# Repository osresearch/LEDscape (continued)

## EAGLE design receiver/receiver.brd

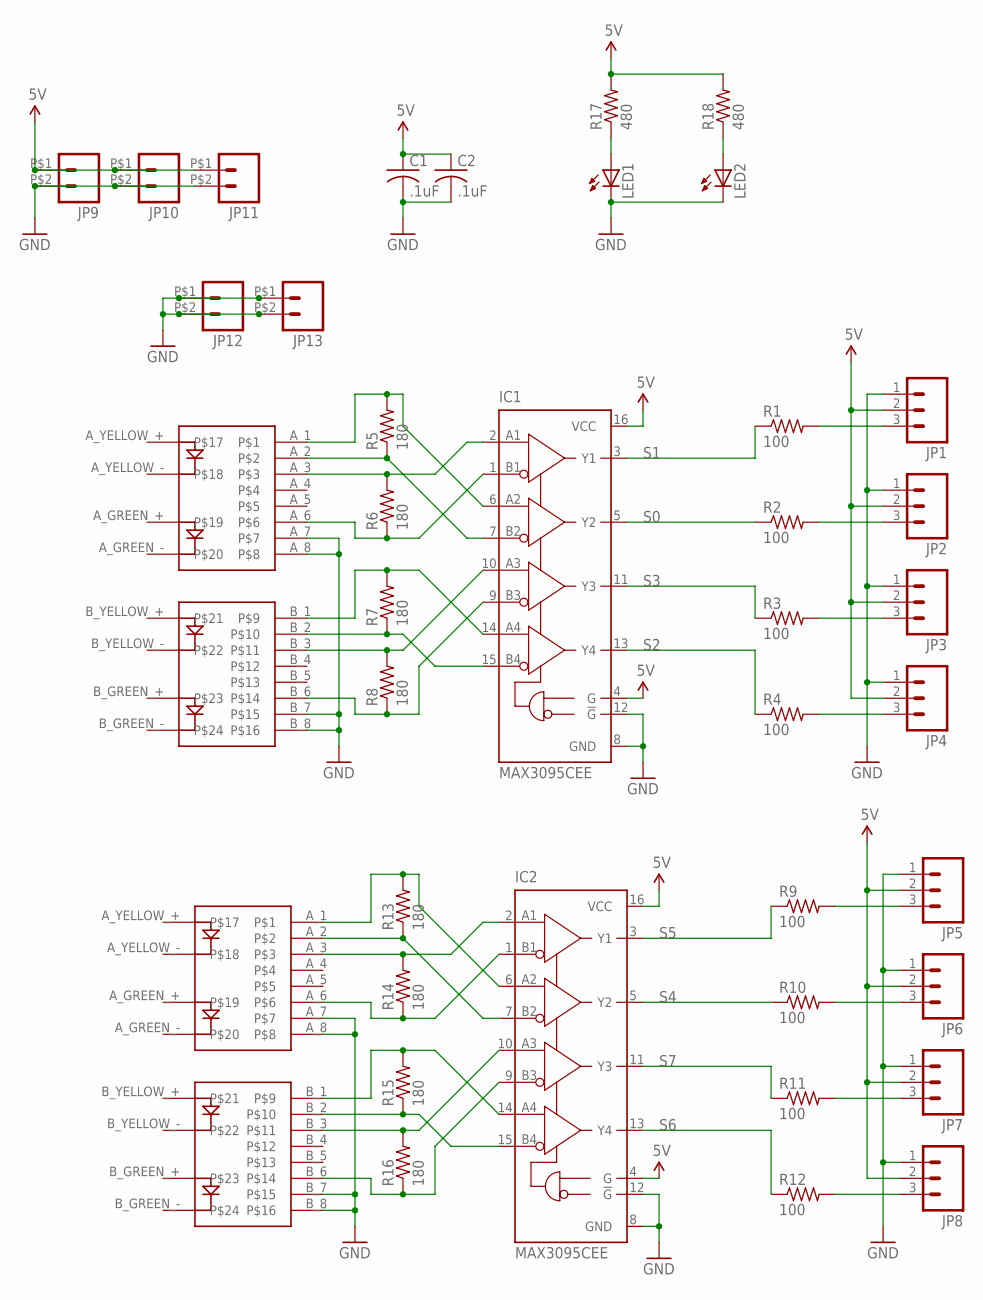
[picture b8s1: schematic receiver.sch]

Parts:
C1, C2: .1uF; C0603
IC1, IC2: MAX3095CEE; QSOP16
JP1, JP2, JP3, JP4, JP5, JP6, JP7, JP8: M03-SCREW-5MM; SCREWTERMINAL-5MM-3
JP9, JP10, JP11, JP12, JP13: M026.35MM; SCREWTERMINAL-6.35MM-2
LED1, LED2: LEDCHIPLED_0805; CHIPLED_0805
R1, R2, R3, R4, R9, R10, R11, R12: 100; R0603
R5, R6, R7, R8, R13, R14, R15, R16: 180; R0603
R17, R18: 480; R0603
U$1, U$2: RJ45_2X1

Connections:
5V: C1.1, C2.1, IC1.4 (G), IC1.16 (VCC), IC2.4 (G), IC2.16 (VCC), JP1.2, JP2.2, JP3.2, JP4.2, JP5.2, JP6.2, JP7.2, JP8.2, JP9.P$1 (1), JP10.P$1 (1), JP11.P$1 (1), R17.2, R18.2
GND: C1.2, C2.2, IC1.8 (GND), IC1.12 (!G), IC2.8 (GND), IC2.12 (!G), JP1.1, JP2.1, JP3.1, JP4.1, JP5.1, JP6.1, JP7.1, JP8.1, JP9.P$2 (2), JP10.P$2 (2), JP11.P$2 (2), JP12.P$1 (1), JP12.P$2 (2), JP13.P$1 (1), JP13.P$2 (2), LED1.C, LED2.C, U$1.A_7, U$1.A_8, U$1.B_7, U$1.B_8, U$2.A_7, U$2.A_8, U$2.B_7, U$2.B_8
unnamed: JP1.3, R1.2
unnamed: IC1.6 (A2), R5.2, U$1.A_1
unnamed: IC1.7 (B2), R5.1, U$1.A_2
unnamed: JP2.3, R2.2
unnamed: JP3.3, R3.2
unnamed: JP4.3, R4.2
unnamed: IC2.6 (A2), R13.2, U$2.A_1
unnamed: IC1.2 (A1), R6.2, U$1.A_3
unnamed: IC1.1 (B1), R6.1, U$1.A_6
unnamed: IC1.14 (A4), R7.2, U$1.B_1
unnamed: IC1.15 (B4), R7.1, U$1.B_2
unnamed: IC1.10 (A3), R8.2, U$1.B_3
unnamed: IC1.9 (B3), R8.1, U$1.B_6
unnamed: IC2.7 (B2), R13.1, U$2.A_2
unnamed: IC2.2 (A1), R14.2, U$2.A_3
unnamed: IC2.1 (B1), R14.1, U$2.A_6
unnamed: IC2.14 (A4), R15.2, U$2.B_1
unnamed: IC2.15 (B4), R15.1, U$2.B_2
unnamed: IC2.10 (A3), R16.2, U$2.B_3
unnamed: IC2.9 (B3), R16.1, U$2.B_6
unnamed: JP5.3, R9.2
unnamed: JP6.3, R10.2
unnamed: JP7.3, R11.2
unnamed: JP8.3, R12.2
unnamed: LED2.A, R18.1
unnamed: LED1.A, R17.1
S0: IC1.5 (Y2), R2.1
S1: IC1.3 (Y1), R1.1
S2: IC1.13 (Y4), R4.1
S3: IC1.11 (Y3), R3.1
S4: IC2.5 (Y2), R10.1
S5: IC2.3 (Y1), R9.1
S6: IC2.13 (Y4), R12.1
S7: IC2.11 (Y3), R11.1

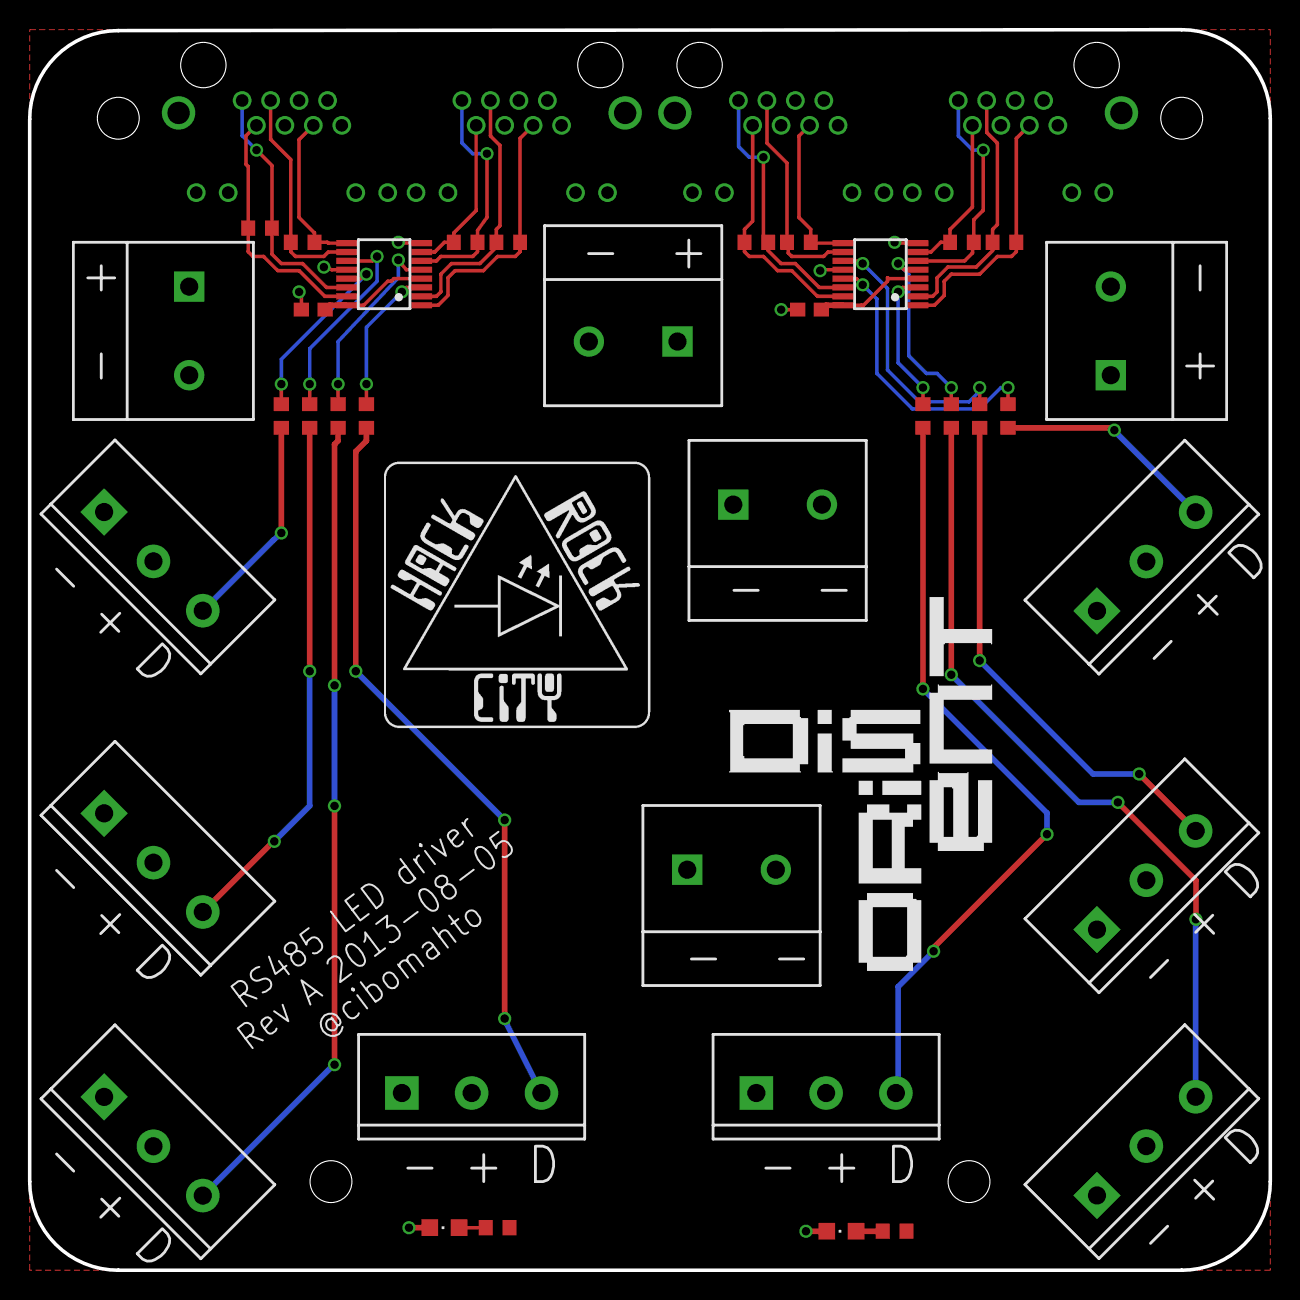
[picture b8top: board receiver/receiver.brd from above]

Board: 2 copper layers, 88.9 x 88.9 mm, 41 parts (0 on the bottom side), 36 nets.

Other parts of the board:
U$3: DISORIENT_LOGO
U$4: HRC_LOGO_0.75IN

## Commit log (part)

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2013-09-30 port of the pyramid Fire to the octascroller
2013-09-30 slow it down, tweak pallete and avoid empty first line
2013-09-30 reset occasionally
2013-10-18 Use ns parameter in WAITNS macro
    I think you meant to use "ns" where you used "lab"
2013-11-22 Move images around
2013-11-22 Remove targets that curently don't build
2013-12-18 ubuntu on bbb
2013-12-18 use binary coded pwm to improve smooth colors
2013-12-18 steeper steps to show more gradation
2013-12-18 rename angstrom dtb
2014-01-08 reworked slightly to adjust position of connectors; ordered via oshpark
2014-01-12 enable pru
2014-01-12 DTS files
2014-01-13 Add interface board and SD card adapter
2014-01-15 Fix brightness so that it is visible on the matrix
2014-01-24 C++ fixes
2014-01-24 import of GPLed perlin noise code and wrapper for ledscape
2014-01-24 brighten it up
2014-01-24 build the perlin demo
2014-01-24 do panel copy in one pass
2014-01-24 fix matrix mode inits
2014-01-25 fix color space for 24-bit rgb
2014-01-27 Drop the isolated receiver design, move the strip pcb design to its own folder, tweak the LEDscape pcb design
2014-01-27 Move receiver board into the pcbs directory
2014-01-27 Add note about different directory in Ubuntu 13.10
2014-01-27 Move examples into their own directories to reduce clutter
2014-01-27 Remove outdated bad-pattern example, move teensy things into their own directory
2014-01-27 Fix permissions on non-executable files
2014-01-27 Move video display code into teensy directory (maybe move all of that code into a different project?)
2014-01-27 Continue reorganizing the build system
2014-01-27 Switch to a Make subdirs style build system, to separate the LEDscape library from the example files.
2014-01-27 Remove old LEDscape.dts file
2014-01-27 Add bone30 version of the dts file (for current, unmodified Ubuntu images)
2014-01-27 Drop old test-bitslice example, update run-ledscape to work with new directory structure
2014-01-27 Update ledscape.c to look for .bin in ../lib (should make this more robust?), and modify the run-ledscape script to move to the correct directory.
2014-01-28 Add GPL2 license
2014-01-28 Add setup instructions for Ubuntu image
2014-02-22 bbb pru config finally works. device tree sucks
2014-02-22 support the 32x32 arrays
2014-02-22 brightness note
2014-02-23 started on MTA sign font
2014-02-23 updated a few chars
2014-02-26 more letters imported
2014-02-26 Fix capemgr for debian
2014-02-26 fix for cube
2014-02-26 turn off the power management features for wifi
2014-02-26 something is not right with the width; glitches at 128?
2014-03-02 life on the cube scroller
2014-03-02 colorful fading
2014-03-02 cube life almost works; edges not quite right yet
2014-03-03 identify is broken? something is wrong with the expected layout
2014-03-03 draw six image faces
2014-03-03 cube life works. frustratingly the mapping is backwards?
2014-03-03 tweak identify routine
2014-03-03 tweak parameters
2014-03-03 rename image-cube to cube-image
2014-03-03 avoid extra prints
2014-03-16 fix r30/r31 overwrite bug
2014-03-16 Fix gpio lines, switch back to 32x16 matrices
2014-03-16 test pwm hardware in dts; not used yet
2014-03-20 flat bracket to connect to 15mm extrusion
2014-03-21 brackets for 15mm mitsum rail
2014-03-22 started on bracket to use 20mm extrusion
2014-03-22 printed for flat
2014-03-23 Identify based on the mta font
2014-03-23 flipping works for vertical panels
2014-03-23 add framebuffer flipping code to deal with zig-zag orientation
2014-03-23 move brightness level to a top-level define
2014-03-23 use framebuffer flipping code for16 matrix panel
2014-03-24 flip the framebuffer for the leds
2014-03-26 Add 'q', ':', ',' to MTA font JSON
2014-03-28 brackets for octoscroller, 8 or 16 sided
2014-03-28 matrix config into a separate routine
2014-03-28 wrapping sort of works
2014-03-28 8 panels of output; should be a config
2014-03-28 config files
2014-03-28 20mm brackets the other way
2014-03-29 matrix-udp-rx works with pyramid and mini-pyramid
2014-04-04 fire rendering works on the mini-pyramid
2014-04-04 full size octoscroller matrix
2014-04-04 full size mini-pyramid
2014-04-04 receive and space the pixels for the mini pyramid
2014-04-07 disable double buffering
2014-04-07 enable life on the full pyramid
2014-04-08 pre-compiled device tree cape
2014-04-13 move everything into subdirectories; makefile is broken for now
2014-04-13 makefiles that sort of work
2014-04-13 makefiles for each subdir, easier targets
2014-04-13 makefile tweaks; things mostly work again
2014-04-13 split strip and matrix code
2014-04-13 move matrix config into ledscape.h
2014-04-13 move matrix remap into ledscape.c
2014-04-13 import a fixed-width 8px font, cleanup unused bitslicing code
2014-04-13 make every binary depend on libledscape.a
2014-04-13 rudimentary matrix config parser
2014-04-14 use config system
2014-04-14 remove last deps on bitslice.h
2014-04-14 empty dir files
2014-04-14 abort if a subdir fails
2014-04-14 top half of single pass remapping works
2014-04-14 removed dead code in matrix draw
2014-04-14 added default matrix config
2014-04-14 default matrix config
2014-04-14 off-by-16 error
2014-04-14 include all panel outputs
2014-04-14 everything builds again
2014-04-14 comment color alignment
2014-04-15 add -g
2014-04-15 change colors, allow config
2014-04-15 fail cleanly
2014-04-15 ws2812 strips work again, although first pixel is noisy
2014-04-15 config cleanup
2014-04-15 resize for strip test
2014-04-19 Add init.d script for starting/stopping LEDscape
2014-04-20 32-sided plate layout
2014-04-20 tall brackets
2014-04-20 tweak parameters a bit
2014-04-20 firmware loader
2014-04-20 remove timer code, move reading from stdin into a separate thread
2014-04-20 knob controller for the perlin noise box
2014-04-20 smaller plate for vertical bracket
2014-04-21 vertical attachment brackets, too
2014-04-21 Hacks and kludges to get the WS2812B working again.
2014-04-21 T-bracket for center section
2014-04-21 life works again
2014-04-21 read four arguments from serial port
2014-04-22 identify does panel/output numbers
2014-04-22 mapped tall cylinder
2014-04-22 update matrix test; this should be an option
2014-04-22 wrap on the cylinder
2014-04-22 matrix-udp-rx works with transmitter code (half the panels)
2014-04-22 include dependency files
2014-04-22 parameters for cylinder; need to make these runtime
2014-04-25 dual frame reception (compatible with megaScrollerTransmitter)
2014-04-25 fire works on the mega scroller
2014-05-06 v1.3 of boards (as ordered)
2014-05-07 make the fire rotate
2014-05-07 brighter!
2014-05-07 getoptified stuff
2014-05-07 timeout works
2014-05-07 option to not call pru_exec() if things are already running
2014-05-07 fix newline handling in ledscape_printf
2014-05-07 silence ledscape_printf
2014-05-14 properly calculate size of buffer
2014-05-15 parameterizing packets per frame
2014-05-15 typo snuck in
2014-05-15 a few more typos
2014-05-16 suggested changes from osr
2014-05-17 Add missing receiver pcb design
2014-05-24 increase startup delay
2014-05-24 default to a 256x128 arrangement
2014-05-24 install script for angstrom
2014-05-24 do not fill up the log
2014-05-24 update the uEnv file, too
2014-05-24 handle case of /media/BEAGLEBONE already being mounted
2014-05-27 Bugfix: compute buffer size specifically, sizeof() on a calloc-created object returns the type size
2014-05-27 Bugfix: allow arbitrary even heights for screen geometry, don't crash if no options, fix fps display
2014-05-27 Add Python-based video player
2014-05-27 Add setup file with some instructions on setting up and using LEDscape
2014-05-27 Add descriptions for config file, command line options
2014-05-31 TCP receiving code
2014-06-01 python test works agian
2014-06-01 using hmason/botomatic to get twitter results
2014-06-02 Point to the Blinkinlabs repo.
2014-06-04 .beats time for @phooky
2014-06-04 Add video player service, bugfix for ledscape service, update instrutions to reference /opt
2014-06-04 Fix location of the service files in the setup instructions
2014-06-04 Add mount detection to USB drive, to be a little more fail tolerant
2014-06-06 two player lightcycles game
2014-08-02 RevB LEDscape board design: slightly bigger, debug headers for all signals
2014-08-02 New receiver design: 4x output instead of 8x output
2014-08-02 Redesign transmitter PCB to use top and bottom ground planes, and one track for +5V- should be much easier to work with.
2014-08-03 Receiver 4x: Rev B design
2014-08-03 Updated BBB footprint, mounting holes in LEDscape baord, small cleanups
2014-08-09 Make consistant whitespace formatting in ws281x.p
2014-08-09 More cleanup and whitespace alignment in ws281x.p
2014-08-09 Reassign GPIOs for WS281x mode
2014-08-22 Fix mapping for new LEDscape board, fix bug in matrix-udp-rx
2014-08-22 Move scripts to src/scripts, remove old udp receiver example
2014-08-22 Add makefile rule to copy scripts, extended setup instructions
2014-08-22 Document upstart startup script
2014-08-22 Add pin assignments chart for LEDscape trasnsmitter board
2014-09-07 create empty bin directory
2014-09-15 Update for 120x32 geometry
2014-09-18 Fixes to allow configuration of 32x32 panels. Fixes to allow configuration of fewer than 8 ports
2014-10-07 brackets for the spiral piece
2015-02-05 Update the configuration to handle a 64x64 display made up of one chain of 4 32x32 panels
2015-02-05 Games in all the wrong directories
2015-02-09 Move ledgames stuff to it's own directory
2015-02-16 Draws some invaders
2015-02-17 Sprites move and animate.
2015-03-07 Fixed offset of second frame part
    Offset was height*frame_part*width, which is on the second frame part height*width, so out of drawing frame. Should be just the second half of the image.
2015-03-09 Automatically build both required dtbo files
2015-03-09 Invaders game progress
2015-03-15 Updated .gitignore to ignore DS_Store files Added in acrylic cutting files
2015-03-15 Remove those files which aren't used for the LEDgames project
2015-03-20 Remove a duplicate
2015-03-22 Invaders is now semi-playable
2015-03-23 Invaders shoot and player takes damage. Animations. Multiplayer fixes
2015-03-29 Support blue/green software flip Move the player 1 right direction to a new pin
2015-03-29 Add resources for games
2015-03-29 Automatically place resources
2015-03-29 Animated ship and ship destruction
2015-03-29 Remove more code not used for the games
2015-03-30 Invaders have scores when shot. Renamed some things. Updated graphics Created menu system
2015-04-26 Menu doesn't exit. Menu range calculated from sprites vector!
2015-04-26 Slow down invader firing. Pixel-accurate collision
2015-04-26 Flip controls for dual player
2015-05-10 Add sounds to invaders mode!
2015-06-10 Update setup instructions
2015-06-12 Bugfixes!
2015-06-12 Height calculation was wrong for udp rx.
2015-06-12 Add read-only fs instrutions
2015-06-12 revert to a default of 64 height in matrix code
2015-06-12 Remove unneeded config example
2015-06-12 Make symbolic links for scripts instead of copying them, in case they are edited later
2015-06-12 Remove outdated wifi config file
2015-06-15 Specificy the correct image to use (Debian, not Ubuntu!)
2015-06-16 Revert the pin assignments to match the LEDscape board
2015-08-18 Add 2x output PCB and LightBuddy output adapter for RS285 testing
2016-03-29 Delete BeagleBone-setup.md
    Outdated file (See #19)
2016-08-01 better identification pattern for strips
2016-12-09 Document configuration values for ws2812 mode
2018-02-25 Introduce a memory barrier between writing the DMA address and the command.
    Without a memory barrier gcc is free to reorder volatile stores. In my case
    the LED strip lit up with uninitialized memory for the first draw and then
    fixed itself with the next one. With this change it was immediately fixed.
2018-10-26 added newline print statement
